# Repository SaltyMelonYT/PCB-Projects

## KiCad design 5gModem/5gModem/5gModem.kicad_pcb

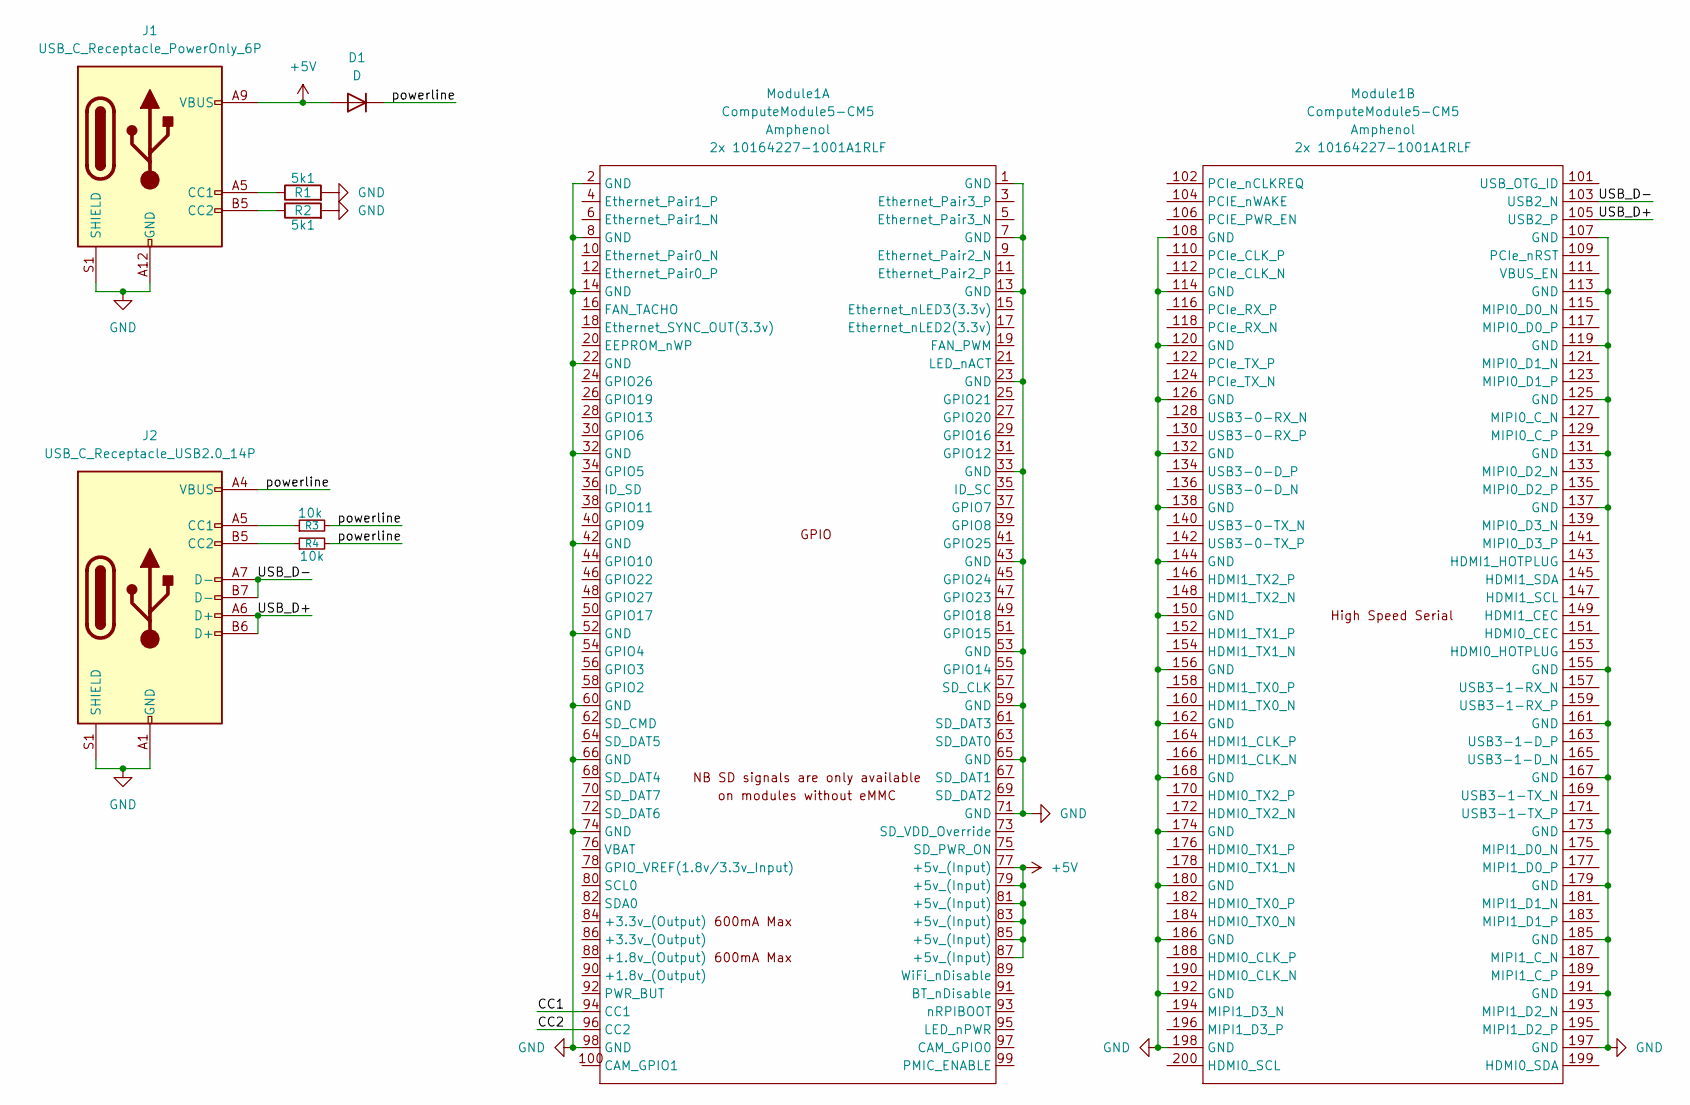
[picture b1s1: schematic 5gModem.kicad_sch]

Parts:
D1: D; D_2010_5025Metric
J1: USB_C_Receptacle_PowerOnly_6P; USB_C_Receptacle_GCT_USB4125-xx-x-0190_6P_TopMnt_Horizontal
J2: USB_C_Receptacle_USB2.0_14P; USB_C_Receptacle_GCT_USB4105-xx-A_16P_TopMnt_Horizontal
Module1: ComputeModule5-CM5; Raspberry-Pi-5-Compute-Module
R1, R2: 5k1; R_1210_3225Metric_Pad1.30x2.65mm_HandSolder
R3, R4: 10k; R_1812_4532Metric

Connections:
+5V: D1.2 (A), J1.A9 (VBUS), J1.B9 (VBUS), Module1.77 (+5v_(Input)), Module1.79 (+5v_(Input)), Module1.81 (+5v_(Input)), Module1.83 (+5v_(Input)), Module1.85 (+5v_(Input)), Module1.87 (+5v_(Input))
/CC1: Module1.94 (CC1)
/CC2: Module1.96 (CC2)
/USB_D+: J2.A6 (D+), J2.B6 (D+), Module1.105 (USB2_P)
/USB_D-: J2.A7 (D-), J2.B7 (D-), Module1.103 (USB2_N)
/powerline: D1.1 (K), J2.A4 (VBUS), J2.A9 (VBUS), J2.B4 (VBUS), J2.B9 (VBUS), R3.2, R4.2
GND: J1.A12 (GND), J1.B12 (GND), J1.S1 (SHIELD), J2.A1 (GND), J2.A12 (GND), J2.B1 (GND), J2.B12 (GND), J2.S1 (SHIELD), Module1.1 (GND), Module1.2 (GND), Module1.7 (GND), Module1.8 (GND), Module1.13 (GND), Module1.14 (GND), Module1.22 (GND), Module1.23 (GND), Module1.32 (GND), Module1.33 (GND), Module1.42 (GND), Module1.43 (GND), Module1.52 (GND), Module1.53 (GND), Module1.59 (GND), Module1.60 (GND), Module1.65 (GND), Module1.66 (GND), Module1.71 (GND), Module1.74 (GND), Module1.98 (GND), Module1.107 (GND), Module1.108 (GND), Module1.113 (GND), Module1.114 (GND), Module1.119 (GND), Module1.120 (GND), Module1.125 (GND), Module1.126 (GND), Module1.131 (GND), Module1.132 (GND), Module1.137 (GND), Module1.138 (GND), Module1.144 (GND), Module1.150 (GND), Module1.155 (GND), Module1.156 (GND), Module1.161 (GND), Module1.162 (GND), Module1.167 (GND), Module1.168 (GND), Module1.173 (GND), Module1.174 (GND), Module1.179 (GND), Module1.180 (GND), Module1.185 (GND), Module1.186 (GND), Module1.191 (GND), Module1.192 (GND), Module1.197 (GND), Module1.198 (GND), R1.2, R2.2
unnamed: J1.A5 (CC1), R1.1
unnamed: J1.B5 (CC2), R2.1
unnamed: J2.A5 (CC1), R3.1
unnamed: J2.B5 (CC2), R4.1

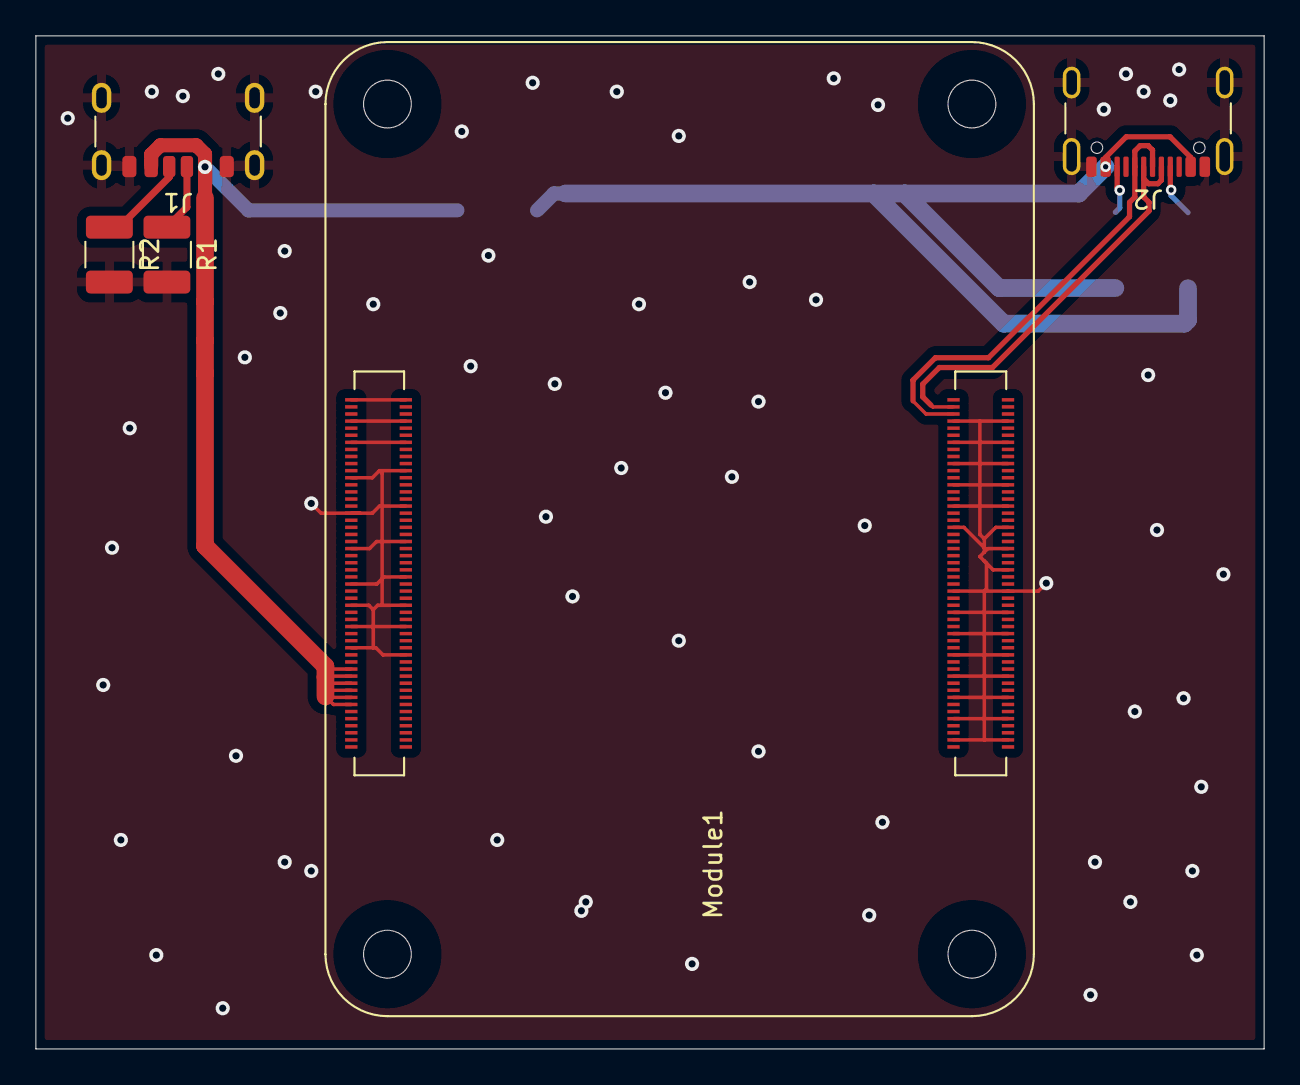
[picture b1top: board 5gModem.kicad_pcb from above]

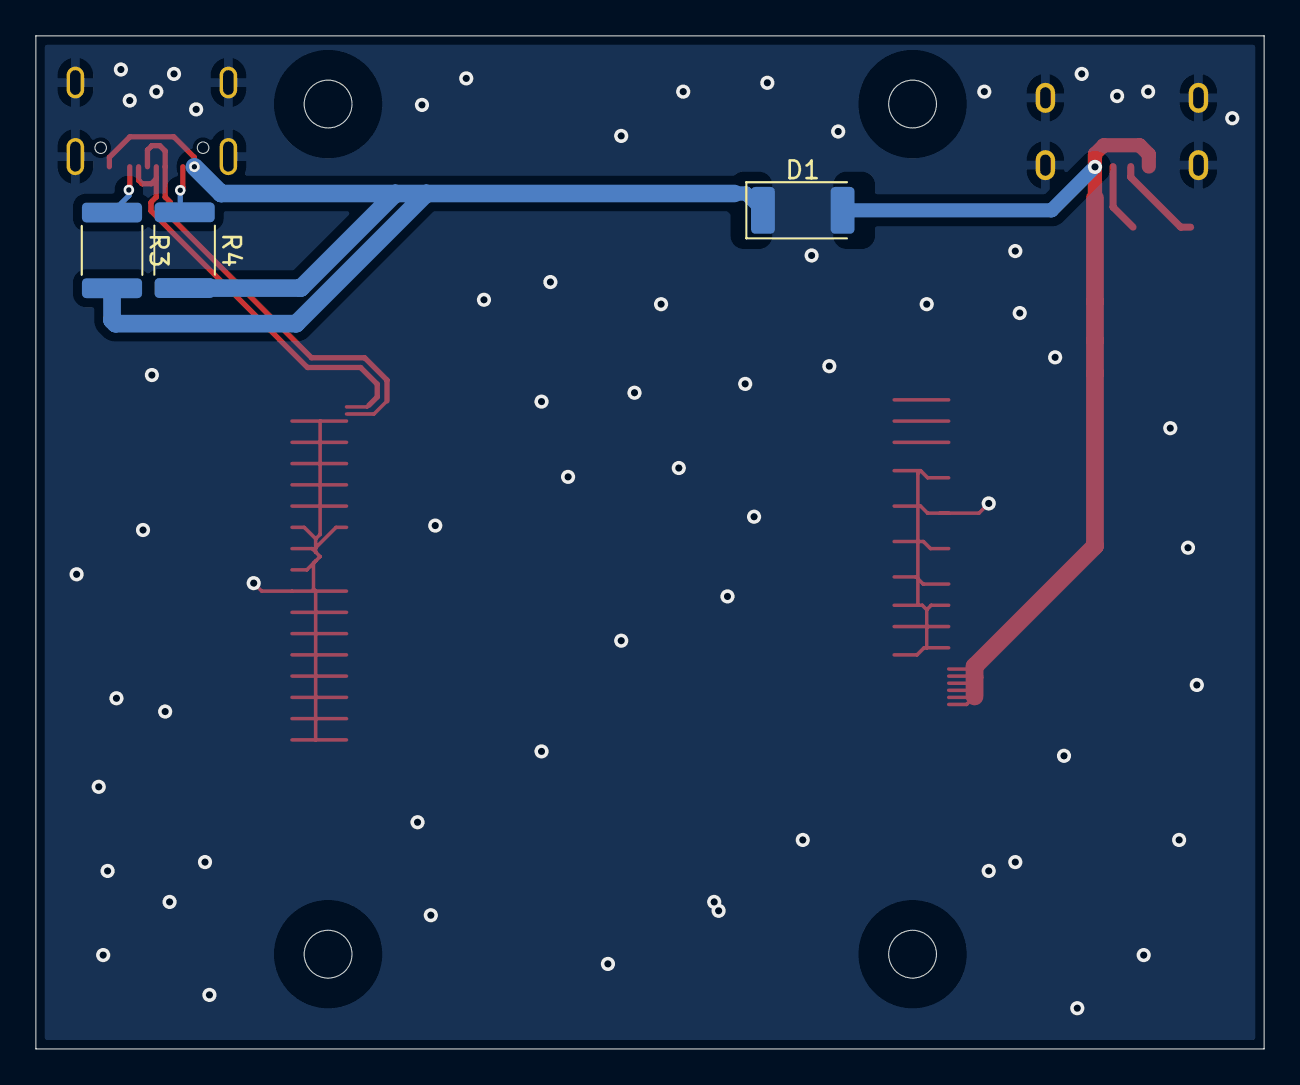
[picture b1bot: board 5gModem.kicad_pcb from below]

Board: 2 copper layers, 69.4 x 57.2 mm, 8 parts (3 on the bottom side), 9 nets.

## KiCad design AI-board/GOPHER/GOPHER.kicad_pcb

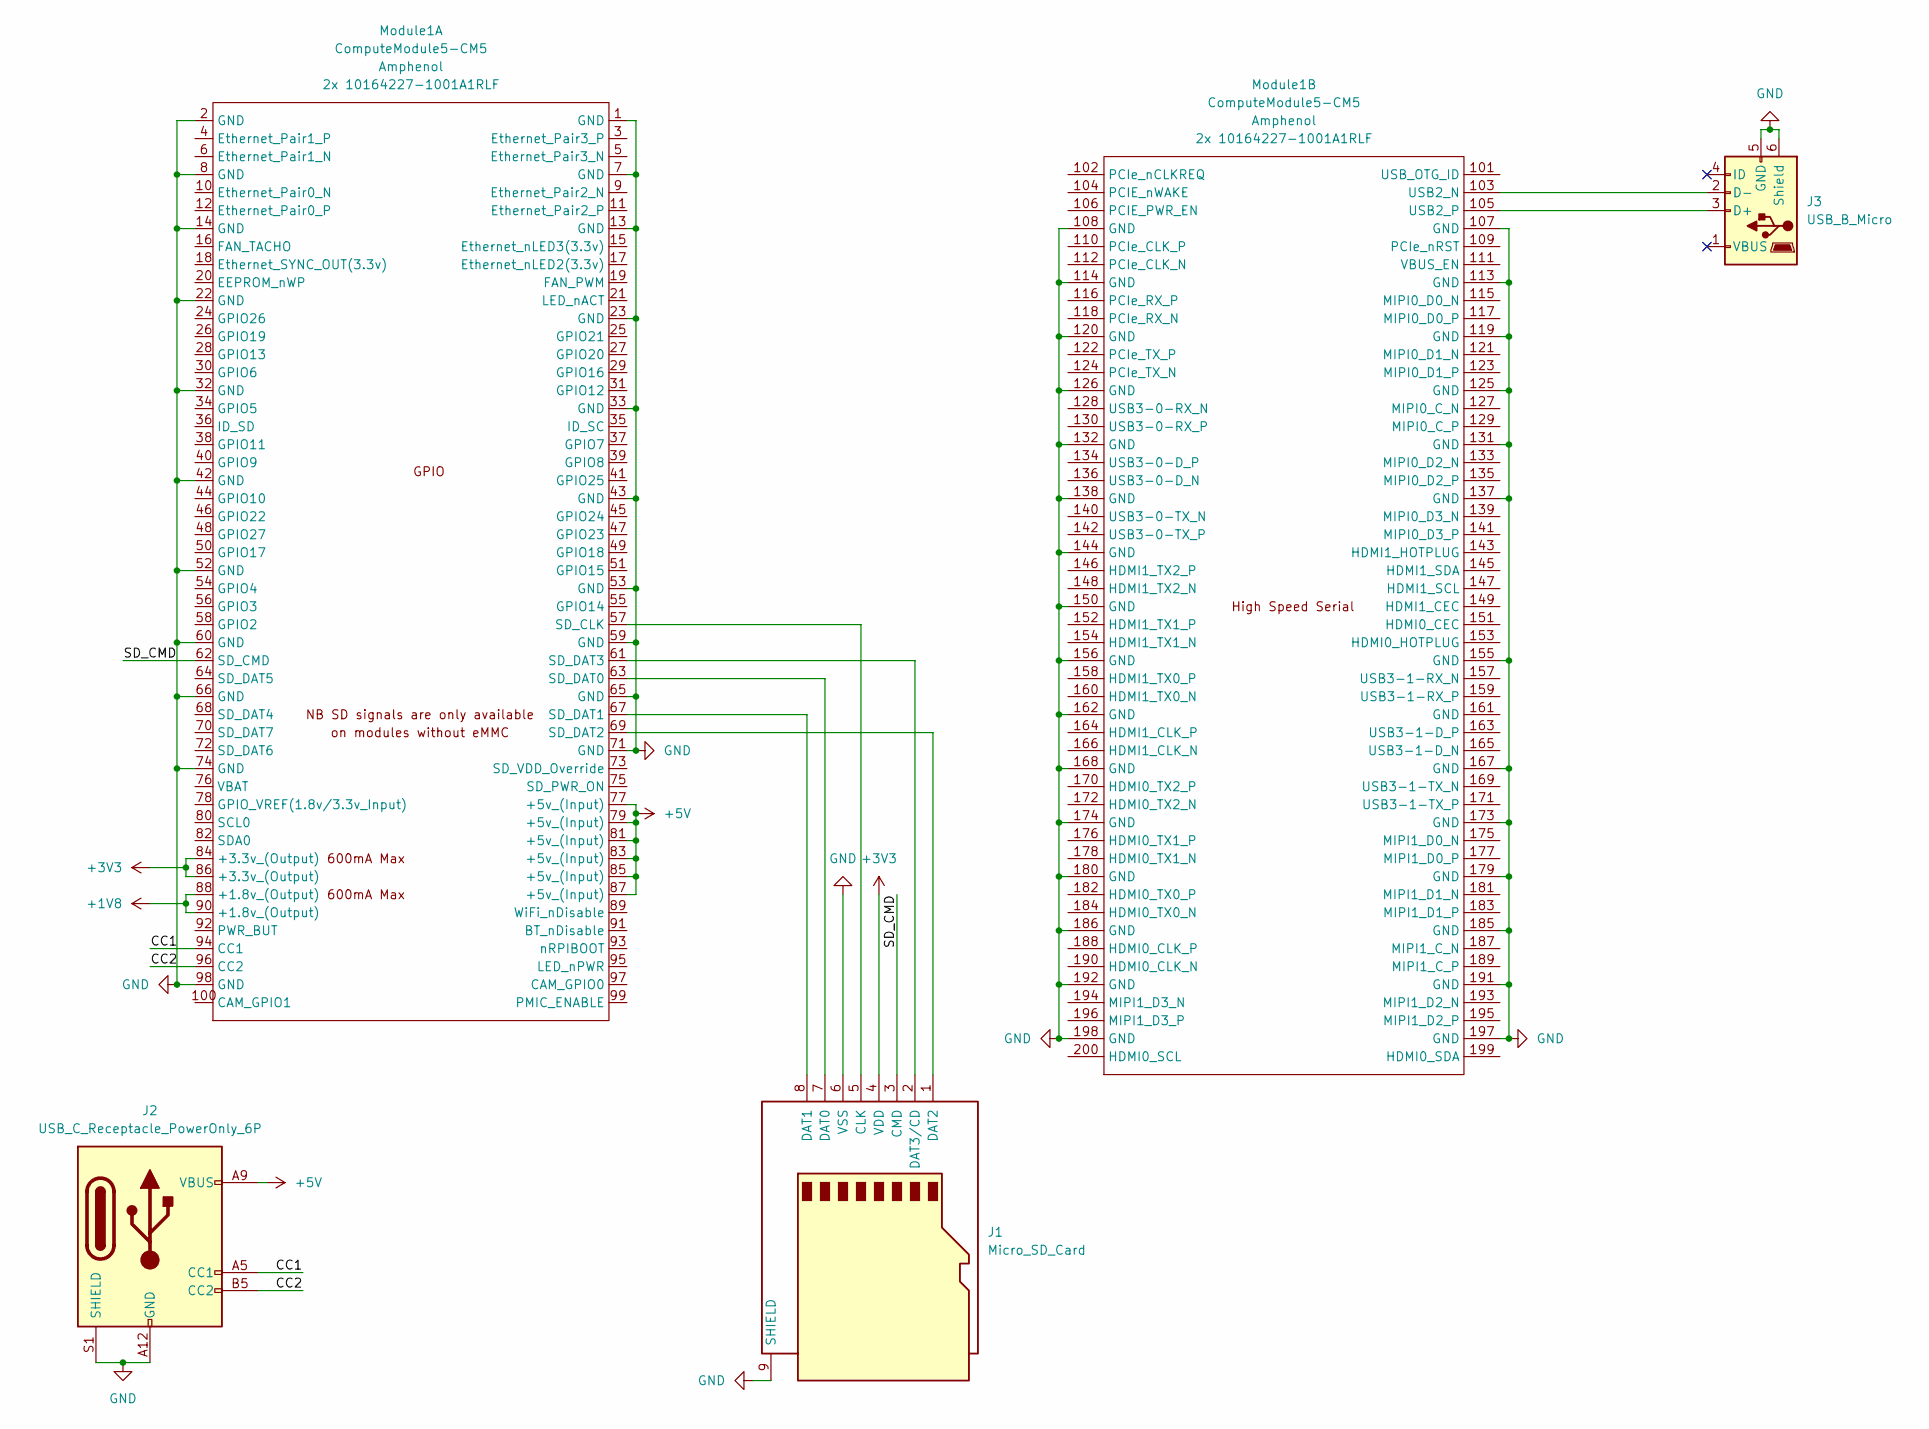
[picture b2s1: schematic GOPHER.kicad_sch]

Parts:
J1: Micro_SD_Card; microSD_HC_Hirose_DM3D-SF
J2: USB_C_Receptacle_PowerOnly_6P; USB_C_Receptacle_GCT_USB4125-xx-x_6P_TopMnt_Horizontal
J3: USB_B_Micro; USB_Micro-B_Amphenol_10103594-0001LF_Horizontal
Module1: ComputeModule5-CM5; Raspberry-Pi-5-Compute-Module

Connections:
+1V8: Module1.88 (+1.8v_(Output)), Module1.90 (+1.8v_(Output))
+3V3: J1.4 (VDD), Module1.84 (+3.3v_(Output)), Module1.86 (+3.3v_(Output))
+5V: J2.A9 (VBUS), J2.B9 (VBUS), Module1.77 (+5v_(Input)), Module1.79 (+5v_(Input)), Module1.81 (+5v_(Input)), Module1.83 (+5v_(Input)), Module1.85 (+5v_(Input)), Module1.87 (+5v_(Input))
/CC1: J2.A5 (CC1), Module1.94 (CC1)
/CC2: J2.B5 (CC2), Module1.96 (CC2)
/SD_CMD: J1.3 (CMD), Module1.62 (SD_CMD)
GND: J1.6 (VSS), J1.9 (SHIELD), J2.A12 (GND), J2.B12 (GND), J2.S1 (SHIELD), J3.5 (GND), J3.6 (Shield), Module1.1 (GND), Module1.2 (GND), Module1.7 (GND), Module1.8 (GND), Module1.13 (GND), Module1.14 (GND), Module1.22 (GND), Module1.23 (GND), Module1.32 (GND), Module1.33 (GND), Module1.42 (GND), Module1.43 (GND), Module1.52 (GND), Module1.53 (GND), Module1.59 (GND), Module1.60 (GND), Module1.65 (GND), Module1.66 (GND), Module1.71 (GND), Module1.74 (GND), Module1.98 (GND), Module1.107 (GND), Module1.108 (GND), Module1.113 (GND), Module1.114 (GND), Module1.119 (GND), Module1.120 (GND), Module1.125 (GND), Module1.126 (GND), Module1.131 (GND), Module1.132 (GND), Module1.137 (GND), Module1.138 (GND), Module1.144 (GND), Module1.150 (GND), Module1.155 (GND), Module1.156 (GND), Module1.162 (GND), Module1.167 (GND), Module1.168 (GND), Module1.173 (GND), Module1.174 (GND), Module1.179 (GND), Module1.180 (GND), Module1.185 (GND), Module1.186 (GND), Module1.191 (GND), Module1.192 (GND), Module1.197 (GND), Module1.198 (GND)
unnamed: J1.5 (CLK), Module1.57 (SD_CLK)
unnamed: J1.7 (DAT0), Module1.63 (SD_DAT0)
unnamed: J1.8 (DAT1), Module1.67 (SD_DAT1)
unnamed: J1.1 (DAT2), Module1.69 (SD_DAT2)
unnamed: J1.2 (DAT3/CD), Module1.61 (SD_DAT3)
unnamed: J3.3 (D+), Module1.105 (USB2_P)
unnamed: J3.2 (D-), Module1.103 (USB2_N)

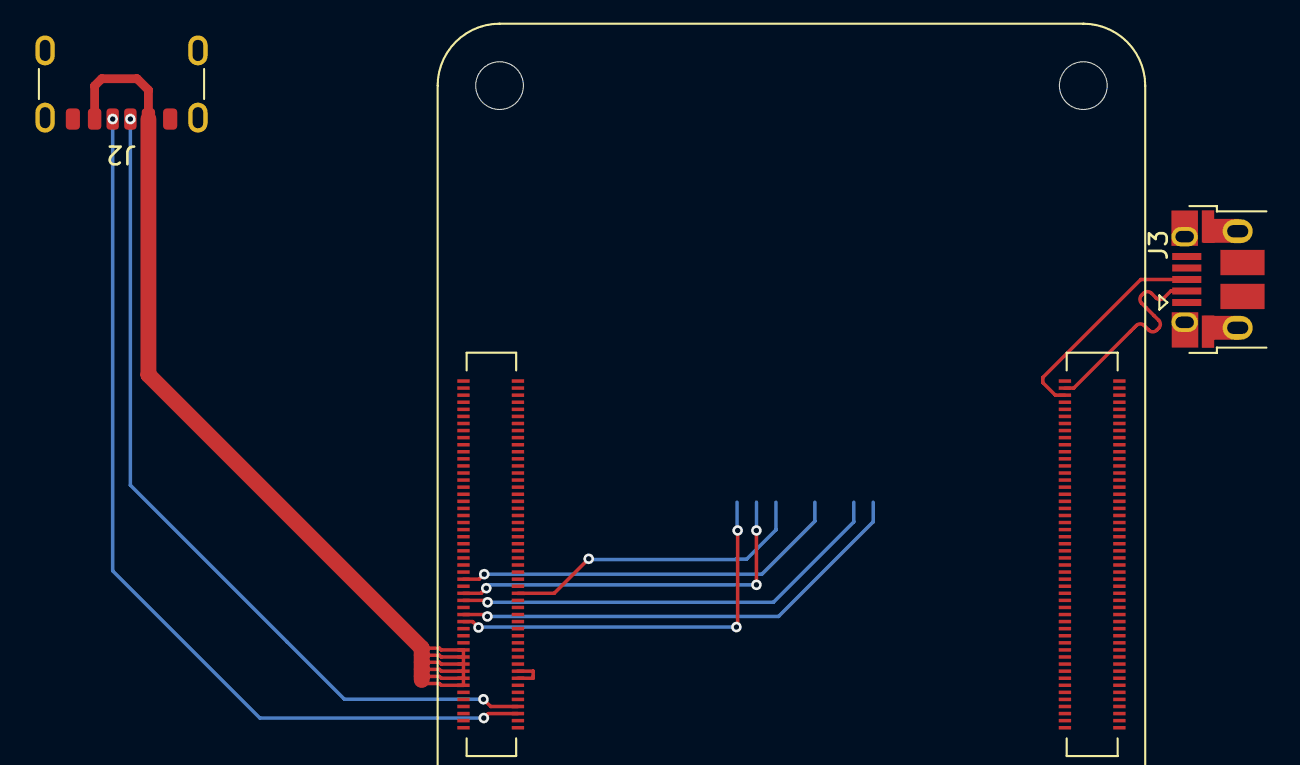
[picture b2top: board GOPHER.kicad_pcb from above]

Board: 2 copper layers, 4 parts (1 on the bottom side), 14 nets.

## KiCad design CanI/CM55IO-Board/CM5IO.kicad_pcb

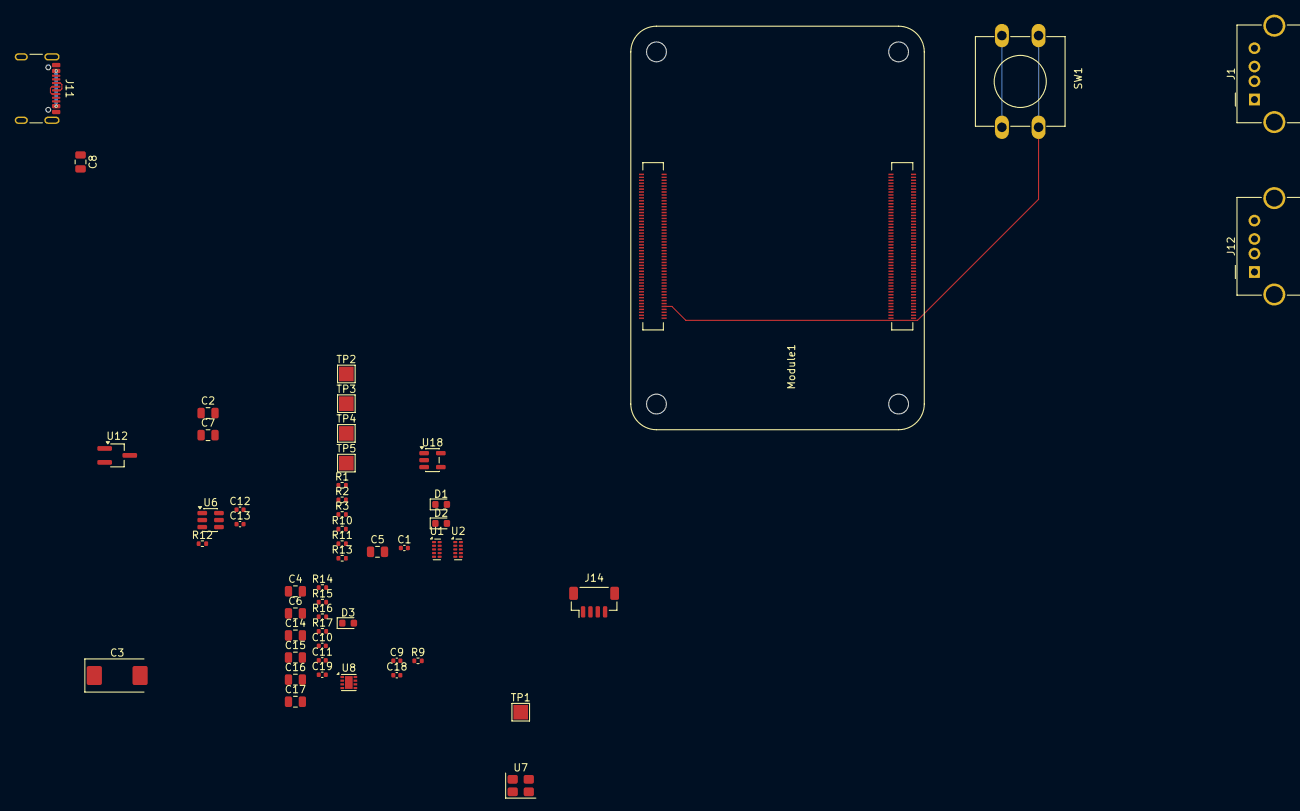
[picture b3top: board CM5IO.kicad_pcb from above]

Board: 2 copper layers, 52 parts (0 on the bottom side), 39 nets.

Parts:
C1, C9, C10, C12, C13, C18, C19: 100n; C_0402_1005Metric
C2, C4, C5, C6, C7, C8, C14, C15, C16, C17: 10u; C_0805_2012Metric
C3: 100uF; CP_EIA-7343-31_Kemet-D
C11: 4.7nF; C_0402_1005Metric
D1: LED Red; LED_0603_1608Metric
D2, D3: LED Green; LED_0603_1608Metric
J1, J12: USB_A; USB_A_Molex_67643_Horizontal
J11: USB_C_Receptacle_USB2.0; USB_C_Receptacle_GCT_USB4105-xx-A_16P_TopMnt_Horizontal
J14: JST_SHBM04B-SRSS-TB; JST_SH_BM04B-SRSS-TB_1x04-1MP_P1.00mm_Vertical
Module1: ComputeModule5-CM5; Raspberry-Pi-5-Compute-Module
R1, R10, R17: 1k; R_0402_1005Metric
R2, R3: 470R; R_0402_1005Metric
R9, R16: 2.2K 1%; R_0402_1005Metric
R11, R13, R15: 10K 1%; R_0402_1005Metric
R12: 15K 1%; R_0402_1005Metric
R14: 100K 1%; R_0402_1005Metric
SW1: Right angle Tact button; SW_PUSH-12mm
TP1, TP2, TP3, TP4, TP5: TestPoint; TestPoint_Pad_2.0x2.0mm
U1, U2: TPD4EUSB30; USON-10_2.5x1.0mm_P0.5mm
U6: AP22653W6; SOT-23-6
U7: ASEK-32.768KHZ-L-R-T; Crystal_SMD_3225-4Pin_3.2x2.5mm
U8: AP3441SHE-7B; DFN-8-1EP_2x2mm_P0.5mm_EP1.05x1.75mm
U12: RT9742SNGV; TSOT-23_HandSoldering
U18: RT9742GGJ5; SOT-23-5

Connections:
/+3.3v: D2.2 (A), Module1.84 (+3.3v_(Output)), Module1.86 (+3.3v_(Output)), R11.1, R13.1, U18.5 (IN)
/+5v: C2.1, C4.1, C6.1, C9.1, C10.1, C12.1, C18.1, J11.A4 (VBUS), J11.A9 (VBUS), J11.B4 (VBUS), J11.B9 (VBUS), J14.1, Module1.77 (+5v_(Input)), Module1.79 (+5v_(Input)), Module1.81 (+5v_(Input)), Module1.83 (+5v_(Input)), Module1.85 (+5v_(Input)), Module1.87 (+5v_(Input)), R9.1, U6.1 (IN), U8.3 (VIN), U12.1 (IN)
/CC1: J11.A5 (CC1), Module1.94 (CC1)
/CC2: J11.B5 (CC2), Module1.96 (CC2)
/CM5_GPIO ( Ethernet, GPIO, SDCARD)/+1.8v: Module1.88 (+1.8v_(Output)), Module1.90 (+1.8v_(Output))
/CM5_GPIO ( Ethernet, GPIO, SDCARD)/ETH_LEDG: Module1.17 (Ethernet_nLED2(3.3v)), R2.2
/CM5_GPIO ( Ethernet, GPIO, SDCARD)/ETH_LEDY: Module1.15 (Ethernet_nLED3(3.3v)), R3.2
/CM5_GPIO ( Ethernet, GPIO, SDCARD)/PWM: J14.2, Module1.19 (FAN_PWM), R11.2, TP2.1
/CM5_GPIO ( Ethernet, GPIO, SDCARD)/PWR_BUT: Module1.92 (PWR_BUT), SW1.1
/CM5_GPIO ( Ethernet, GPIO, SDCARD)/SD_PWR: C5.1, U18.1 (OUT)
/CM5_GPIO ( Ethernet, GPIO, SDCARD)/SD_PWR_ON: Module1.75 (SD_PWR_ON), R13.2, U18.4 (EN)
/CM5_GPIO ( Ethernet, GPIO, SDCARD)/TACHO: J14.4, Module1.16 (FAN_TACHO), TP4.1
/CM5_GPIO ( Ethernet, GPIO, SDCARD)/TRD0_N: Module1.10 (Ethernet_Pair0_N), U2.4 (D2+), U2.7
/CM5_GPIO ( Ethernet, GPIO, SDCARD)/TRD0_P: Module1.12 (Ethernet_Pair0_P), U2.5 (D2-), U2.6
/CM5_GPIO ( Ethernet, GPIO, SDCARD)/TRD1_N: Module1.6 (Ethernet_Pair1_N), U2.2 (D1-), U2.9
/CM5_GPIO ( Ethernet, GPIO, SDCARD)/TRD1_P: Module1.4 (Ethernet_Pair1_P), U2.1 (D1+), U2.10
/CM5_GPIO ( Ethernet, GPIO, SDCARD)/TRD2_N: Module1.9 (Ethernet_Pair2_N), U1.4 (D2+), U1.7
/CM5_GPIO ( Ethernet, GPIO, SDCARD)/TRD2_P: Module1.11 (Ethernet_Pair2_P), U1.5 (D2-), U1.6
/CM5_GPIO ( Ethernet, GPIO, SDCARD)/TRD3_N: Module1.5 (Ethernet_Pair3_N), U1.2 (D1-), U1.9
/CM5_GPIO ( Ethernet, GPIO, SDCARD)/TRD3_P: Module1.3 (Ethernet_Pair3_P), U1.1 (D1+), U1.10
/CM5_GPIO ( Ethernet, GPIO, SDCARD)/nPWR_LED: Module1.95 (LED_nPWR), R10.2
/CM5_HighSpeed/HDMI_5v: C13.1, U12.2 (OUT)
/CM5_HighSpeed/PCIE_PWR_EN: Module1.106 (PCIE_PWR_EN), R14.1, U8.7 (EN)
/CM5_HighSpeed/USB3-0-D_N: J1.2 (D-), Module1.136 (USB3-0-D_N)
/CM5_HighSpeed/USB3-0-D_P: J1.3 (D+), Module1.134 (USB3-0-D_P)
/CM5_HighSpeed/USB3-1-D_N: J12.2 (D-), Module1.165 (USB3-1-D_N)
/CM5_HighSpeed/USB3-1-D_P: J12.3 (D+), Module1.163 (USB3-1-D_P)
/CM5_HighSpeed/VBUS: C3.1, C7.1, C8.1, J1.1 (VBUS), J12.1 (VBUS), U6.6 (OUT)
/CM5_HighSpeed/VBUS_EN: Module1.111 (VBUS_EN), U6.3 (EN)
/PCIe-M2/FB: C11.2, R15.2, R16.1, U8.1 (FB)
/PCIe-M2/M2_3v3: C11.1, C14.1, C15.1, C16.1, C17.1, C19.1, D3.2 (A), R15.1, U7.1 (EN), U7.4 (VDD)
/USB2_N: J11.A7 (D-), J11.B7 (D-), Module1.103 (USB2_N)
/USB2_P: J11.A6 (D+), J11.B6 (D+), Module1.105 (USB2_P)
GND: C1.2, C2.2, C3.2, C4.2, C5.2, C6.2, C7.2, C8.2, C9.2, C10.2, C12.2, C13.2, C14.2, C15.2, C16.2, C17.2, C18.2, C19.2, J1.4 (GND), J1.5 (Shield), J11.A1 (GND), J11.A12 (GND), J11.B1 (GND), J11.B12 (GND), J11.S1 (SHIELD), J12.4 (GND), J12.5 (Shield), J14.3, Module1.1 (GND), Module1.2 (GND), Module1.7 (GND), Module1.8 (GND), Module1.13 (GND), Module1.14 (GND), Module1.22 (GND), Module1.23 (GND), Module1.32 (GND), Module1.33 (GND), Module1.42 (GND), Module1.43 (GND), Module1.52 (GND), Module1.53 (GND), Module1.59 (GND), Module1.60 (GND), Module1.65 (GND), Module1.66 (GND), Module1.71 (GND), Module1.74 (GND), Module1.98 (GND), Module1.107 (GND), Module1.108 (GND), Module1.113 (GND), Module1.114 (GND), Module1.119 (GND), Module1.120 (GND), Module1.125 (GND), Module1.126 (GND), Module1.131 (GND), Module1.132 (GND), Module1.137 (GND), Module1.138 (GND), Module1.144 (GND), Module1.150 (GND), Module1.155 (GND), Module1.156 (GND), Module1.161 (GND), Module1.162 (GND), Module1.167 (GND), Module1.168 (GND), Module1.173 (GND), Module1.174 (GND), Module1.179 (GND), Module1.180 (GND), Module1.185 (GND), Module1.186 (GND), Module1.191 (GND), Module1.192 (GND), Module1.197 (GND), Module1.198 (GND), R9.2, R12.2, R14.2, R16.2, SW1.2, U1.3 (GND), U1.8 (GND), U2.3 (GND), U2.8 (GND), U6.2 (GND), U7.2 (GND), U8.4 (PGND), U8.8 (SGND), U8.9 (PAD), U12.3 (GND), U18.2 (GND)
unnamed: D1.1 (K), R10.1, TP5.1
unnamed: D2.1 (K), R1.1, TP3.1
unnamed: D3.1 (K), R17.1, TP1.1
unnamed: Module1.21 (LED_nACT), R1.2
unnamed: R12.1, U6.5 (ILIM)

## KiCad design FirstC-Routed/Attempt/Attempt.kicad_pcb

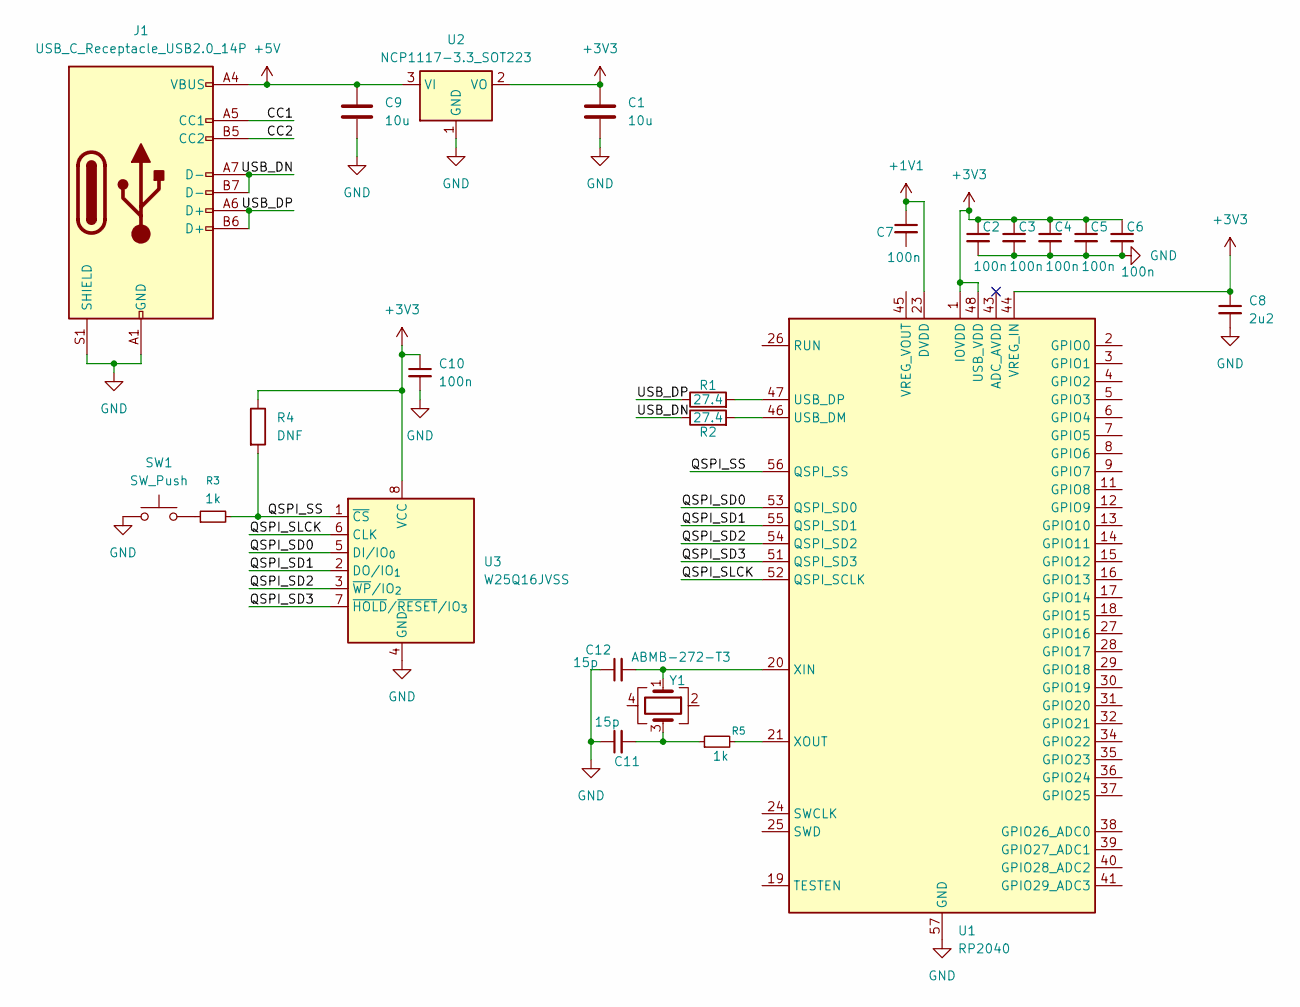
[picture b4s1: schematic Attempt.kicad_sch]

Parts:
C1, C9: 10u; C_0201_0603Metric_Pad0.64x0.40mm_HandSolder
C2, C3, C4, C5, C6, C7, C10: 100n; C_0201_0603Metric_Pad0.64x0.40mm_HandSolder
C8: 2u2; C_0201_0603Metric_Pad0.64x0.40mm_HandSolder
C11, C12: 15p; C_0201_0603Metric_Pad0.64x0.40mm_HandSolder
J1: USB_C_Receptacle_USB2.0_14P; USB_C_Receptacle_GCT_USB4105-xx-A_16P_TopMnt_Horizontal
R1, R2: 27.4; R_0402_1005Metric_Pad0.72x0.64mm_HandSolder
R3, R5: 1k; R_0402_1005Metric_Pad0.72x0.64mm_HandSolder
R4: DNF; R_0402_1005Metric_Pad0.72x0.64mm_HandSolder
SW1: SW_Push; SW_PUSH_6mm_H5mm
U1: RP2040; QFN-56-1EP_7x7mm_P0.4mm_EP3.2x3.2mm
U2: NCP1117-3.3_SOT223; SOT-223-3_TabPin2
U3: W25Q16JVSS; SOIC-8_5.3x5.3mm_P1.27mm
Y1: ABMB-272-T3; Crystal_SMD_Abracon_ABS25-4Pin_8.0x3.8mm

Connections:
+1V1: C7.1, U1.23 (DVDD), U1.50 (DVDD)
+3V3: C1.1, C2.1, C3.1, C4.1, C5.1, C6.1, C8.1, C10.1, R4.1, U1.1 (IOVDD), U1.10 (IOVDD), U1.22 (IOVDD), U1.33 (IOVDD), U1.42 (IOVDD), U1.44 (VREG_IN), U1.48 (USB_VDD), U1.49 (IOVDD), U2.2 (VO), U3.8 (VCC)
+5V: C9.1, J1.A4 (VBUS), J1.A9 (VBUS), J1.B4 (VBUS), J1.B9 (VBUS), U2.3 (VI)
/CC1: J1.A5 (CC1)
/CC2: J1.B5 (CC2)
/QSPI_SD0: U1.53 (QSPI_SD0), U3.5 (DI/IO_{0})
/QSPI_SD1: U1.55 (QSPI_SD1), U3.2 (DO/IO_{1})
/QSPI_SD2: U1.54 (QSPI_SD2), U3.3 (~WP/IO_{2})
/QSPI_SD3: U1.51 (QSPI_SD3), U3.7 (~HOLD/~RESET/IO_{3})
/QSPI_SLCK: U1.52 (QSPI_SCLK), U3.6 (CLK)
/QSPI_SS: R3.2, R4.2, U1.56 (QSPI_SS), U3.1 (~CS)
/USB_DN: J1.A7 (D-), J1.B7 (D-), R2.1
/USB_DP: J1.A6 (D+), J1.B6 (D+), R1.1
GND: C1.2, C2.2, C3.2, C4.2, C5.2, C6.2, C8.2, C9.2, C10.2, C11.1, C12.1, J1.A1 (GND), J1.A12 (GND), J1.B1 (GND), J1.B12 (GND), J1.S1 (SHIELD), SW1.1, U1.57 (GND), U2.1 (GND), U3.4 (GND)
unnamed: C11.2, R5.1, Y1.3
unnamed: R3.1, SW1.2
unnamed: R2.2, U1.46 (USB_DM)
unnamed: R1.2, U1.47 (USB_DP)
unnamed: C12.2, U1.20 (XIN), Y1.1
unnamed: R5.2, U1.21 (XOUT)

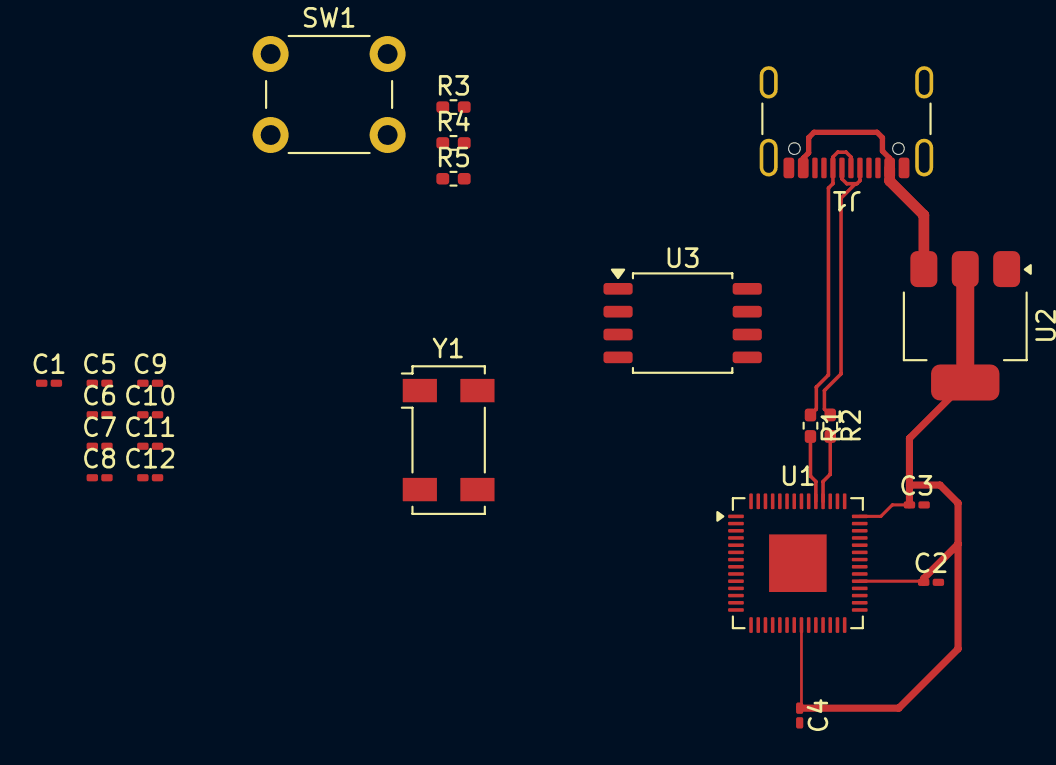
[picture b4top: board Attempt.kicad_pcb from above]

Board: 2 copper layers, 23 parts (0 on the bottom side), 18 nets.

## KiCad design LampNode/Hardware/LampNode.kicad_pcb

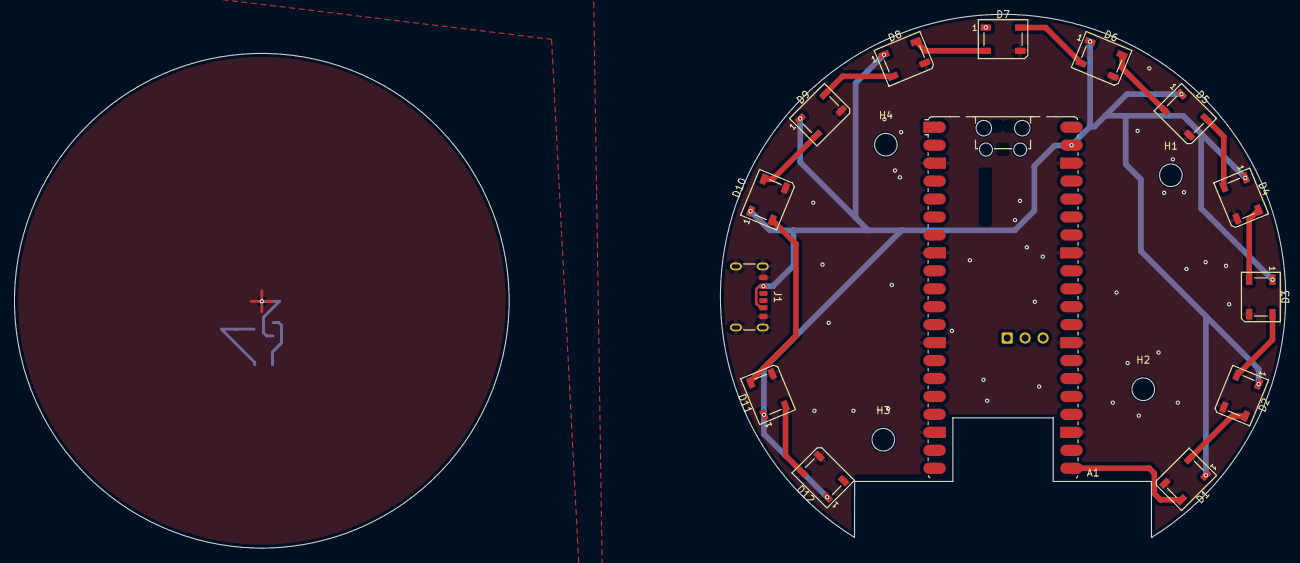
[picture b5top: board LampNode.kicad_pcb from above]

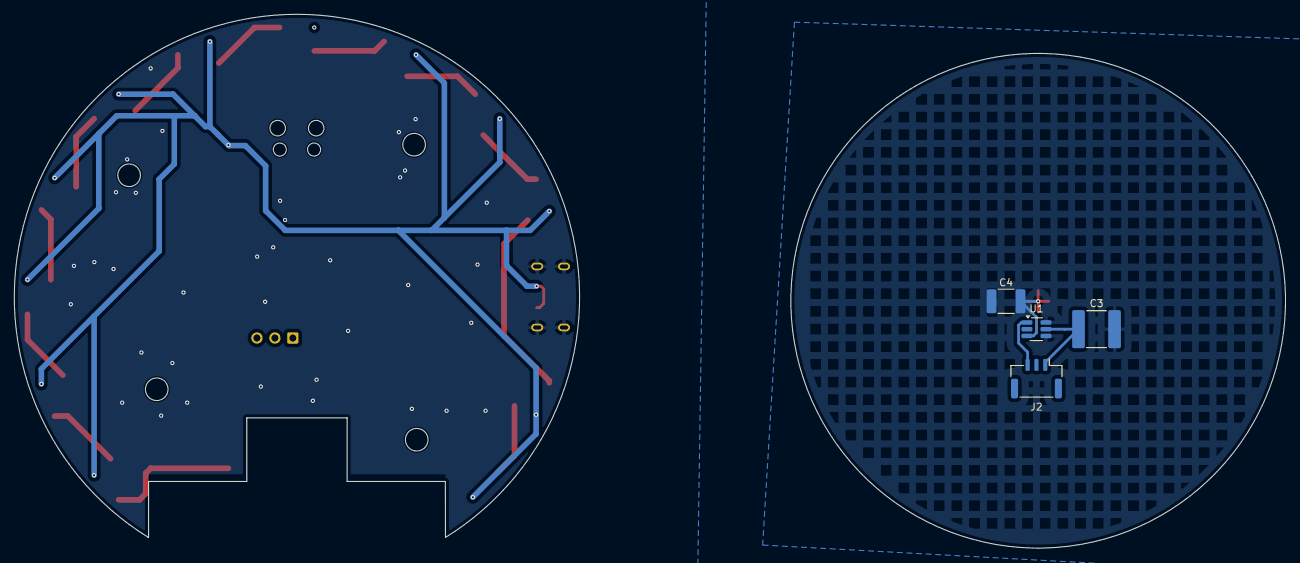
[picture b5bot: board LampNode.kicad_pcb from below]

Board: 2 copper layers, 179.9 x 75.5 mm, 22 parts (4 on the bottom side), 17 nets.

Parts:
A1: RaspberryPi_Pico_W; RaspberryPi_Pico_W_SMD_HandSolder
C3: C_Small; C_2220_5750Metric
C4: 25pF; C_1812_4532Metric
D1, D2, D3, D4, D5, D6, D7, D8, D9, D10, D11, D12: WS2812B; LED_WS2812B_PLCC4_5.0x5.0mm_P3.2mm
H1, H2, H3, H4: MountingHole; MountingHole_3.2mm_M3
J1: USB_C_Receptacle_PowerOnly_6P; USB_C_Receptacle_GCT_USB4125-xx-x-0190_6P_TopMnt_Horizontal
J2: Conn_01x03; JST_GH_BM03B-GHS-TBT_1x03-1MP_P1.25mm_Vertical
U1: TTP223-BG; SOT-23-6_Handsoldering

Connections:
+5V: A1.39 (VSYS), D1.1 (VDD), D2.1 (VDD), D3.1 (VDD), D4.1 (VDD), D5.1 (VDD), D6.1 (VDD), D7.1 (VDD), D8.1 (VDD), D9.1 (VDD), D10.1 (VDD), D11.1 (VDD), D12.1 (VDD), J1.A9 (VBUS), J1.B9 (VBUS)
GND: A1.3 (GND), A1.8 (GND), A1.13 (GND), A1.18 (GND), A1.23 (GND), A1.28 (GND), A1.33 (AGND), A1.38 (GND), C3.2, C4.1, D1.3 (VSS), D2.3 (VSS), D3.3 (VSS), D4.3 (VSS), D5.3 (VSS), D6.3 (VSS), D7.3 (VSS), D8.3 (VSS), D9.3 (VSS), D10.3 (VSS), D11.3 (VSS), D12.3 (VSS), J1.A12 (GND), J1.B12 (GND), J1.S1 (SHIELD), U1.2 (VSS), U1.4 (AHLB), U1.6 (TOG)
unnamed: A1.21 (GPIO16), D1.4 (DIN)
unnamed: D1.2 (DOUT), D2.4 (DIN)
unnamed: D2.2 (DOUT), D3.4 (DIN)
unnamed: D3.2 (DOUT), D4.4 (DIN)
unnamed: D4.2 (DOUT), D5.4 (DIN)
unnamed: D5.2 (DOUT), D6.4 (DIN)
unnamed: D6.2 (DOUT), D7.4 (DIN)
unnamed: D7.2 (DOUT), D8.4 (DIN)
unnamed: D8.2 (DOUT), D9.4 (DIN)
unnamed: D9.2 (DOUT), D10.4 (DIN)
unnamed: D10.2 (DOUT), D11.4 (DIN)
unnamed: D11.2 (DOUT), D12.4 (DIN)
unnamed: C3.1, J2.1, U1.5 (VDD)
unnamed: J2.3, U1.1 (Q)
unnamed: C4.2, U1.3 (I)
